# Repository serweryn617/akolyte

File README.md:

# Akolyte

⌨️ Low profile mechanical split keyboard

---

## Building firmware

Prerequisites:
 - `docker`

Firmware can be built using [cook-builder](https://github.com/serweryn617/cook):

**Setup:** initialize submodules and build Docker image. Has to be run only once:

```bash
cook setup
```

**Build:** build everything. Output files will be copied to the `output` directory:

```bash
cook
```

For complete list of commands run `cook -i`.

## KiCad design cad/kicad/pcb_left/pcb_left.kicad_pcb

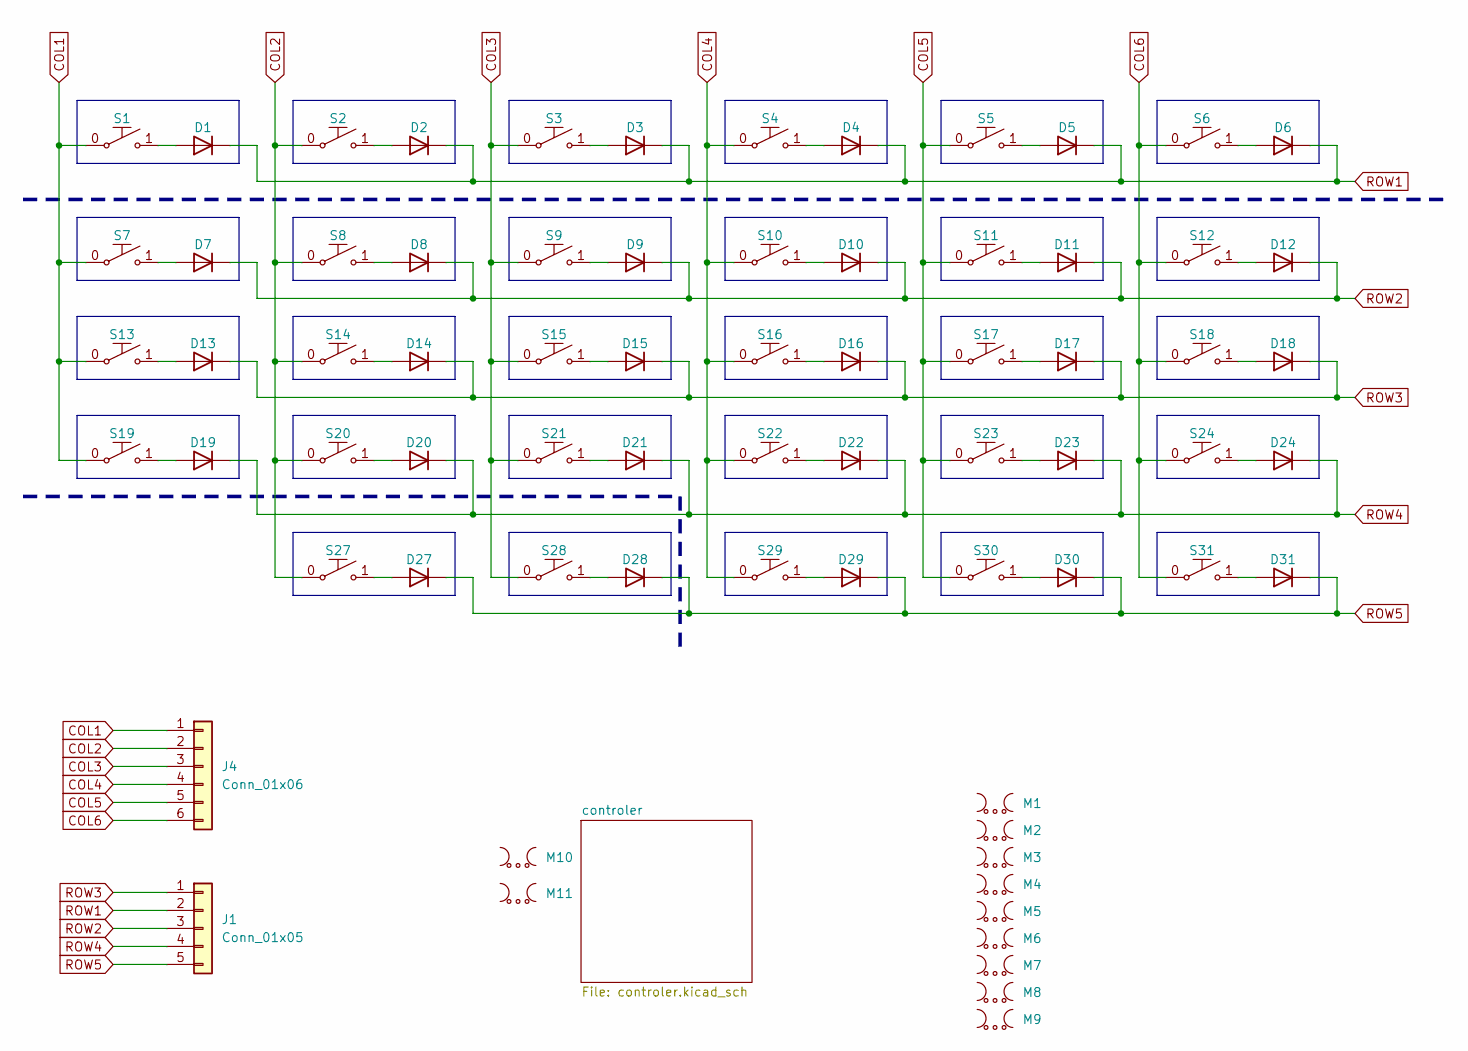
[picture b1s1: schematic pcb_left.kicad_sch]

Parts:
D1, D2, D3, D4, D5, D6, D7, D8, D9, D10, D11, D12, D13, D14, D15, D16, D17, D18, D19, D20, D21, D22, D23, D24, D27, D28, D29, D30, D31: 1N4148; SOD80_P5.5mm_Horizontal_SMD
J1: Conn_01x05; Row Connector
J4: Conn_01x06; Column Connector
M1, M2, M3, M4, M5, M6, M7, M8, M9, M10, M11: Mouse Bites
S1, S2, S3, S4, S5, S6, S7, S8, S9, S10, S11, S12, S13, S14, S15, S16, S17, S18, S19, S20, S21, S22, S23, S24, S27, S28, S29, S30, S31: Gateron_Switch; GATERON

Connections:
COL1: J4.1, S1.0, S7.0, S13.0, S19.0; also elsewhere on the board
COL2: J4.2, S2.0, S8.0, S14.0, S20.0, S27.0; also elsewhere on the board
COL3: J4.3, S3.0, S9.0, S15.0, S21.0, S28.0; also elsewhere on the board
COL4: J4.4, S4.0, S10.0, S16.0, S22.0, S29.0; also elsewhere on the board
COL5: J4.5, S5.0, S11.0, S17.0, S23.0, S30.0; also elsewhere on the board
COL6: J4.6, S6.0, S12.0, S18.0, S24.0, S31.0; also elsewhere on the board
unnamed: D1.2 (A), S1.1
unnamed: D2.2 (A), S2.1
unnamed: D3.2 (A), S3.1
unnamed: D4.2 (A), S4.1
unnamed: D5.2 (A), S5.1
unnamed: D6.2 (A), S6.1
unnamed: D7.2 (A), S7.1
unnamed: D8.2 (A), S8.1
unnamed: D9.2 (A), S9.1
unnamed: D10.2 (A), S10.1
unnamed: D11.2 (A), S11.1
unnamed: D12.2 (A), S12.1
unnamed: D13.2 (A), S13.1
unnamed: D14.2 (A), S14.1
unnamed: D15.2 (A), S15.1
unnamed: D16.2 (A), S16.1
unnamed: D17.2 (A), S17.1
unnamed: D18.2 (A), S18.1
unnamed: D19.2 (A), S19.1
unnamed: D20.2 (A), S20.1
unnamed: D21.2 (A), S21.1
unnamed: D22.2 (A), S22.1
unnamed: D23.2 (A), S23.1
unnamed: D24.2 (A), S24.1
unnamed: D27.2 (A), S27.1
unnamed: D28.2 (A), S28.1
unnamed: D29.2 (A), S29.1
unnamed: D30.2 (A), S30.1
unnamed: D31.2 (A), S31.1
ROW1: D1.1 (K), D2.1 (K), D3.1 (K), D4.1 (K), D5.1 (K), D6.1 (K), J1.2; also elsewhere on the board
ROW2: D7.1 (K), D8.1 (K), D9.1 (K), D10.1 (K), D11.1 (K), D12.1 (K), J1.3; also elsewhere on the board
ROW3: D13.1 (K), D14.1 (K), D15.1 (K), D16.1 (K), D17.1 (K), D18.1 (K), J1.1; also elsewhere on the board
ROW4: D19.1 (K), D20.1 (K), D21.1 (K), D22.1 (K), D23.1 (K), D24.1 (K), J1.4; also elsewhere on the board
ROW5: D27.1 (K), D28.1 (K), D29.1 (K), D30.1 (K), D31.1 (K), J1.5; also elsewhere on the board

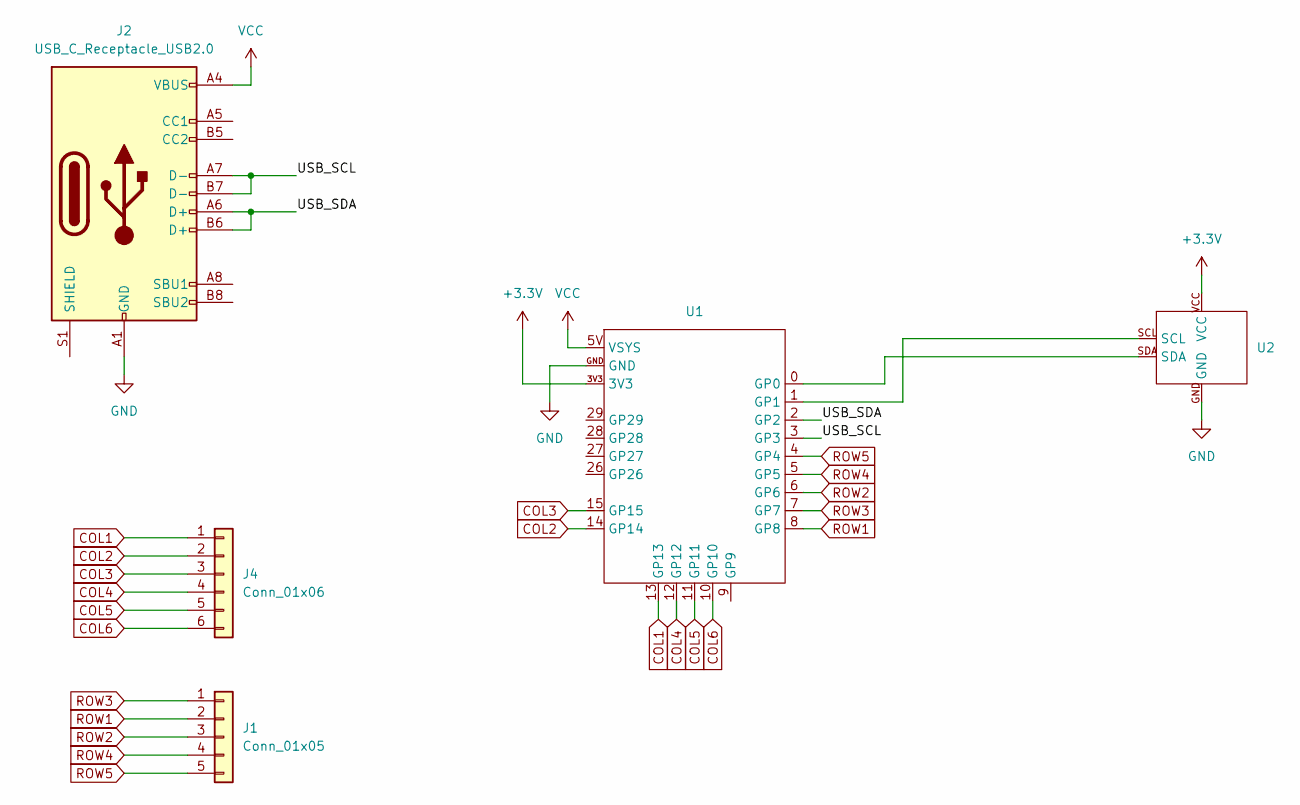
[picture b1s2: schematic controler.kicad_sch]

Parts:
J1: Conn_01x05; Row Connector
J2: USB_C_Receptacle_USB2.0; USB C Port
J4: Conn_01x06; Column Connector
U1: RP2040 - Zero
U2: OLED

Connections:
+3.3V: U1.3V3, U2.VCC
/controler/USB_SCL: J2.A7 (D-), J2.B7 (D-), U1.3 (GP3)
/controler/USB_SDA: J2.A6 (D+), J2.B6 (D+), U1.2 (GP2)
COL1: J4.1, U1.13 (GP13); also elsewhere on the board
COL2: J4.2, U1.14 (GP14); also elsewhere on the board
COL3: J4.3, U1.15 (GP15); also elsewhere on the board
COL4: J4.4, U1.12 (GP12); also elsewhere on the board
COL5: J4.5, U1.11 (GP11); also elsewhere on the board
COL6: J4.6, U1.10 (GP10); also elsewhere on the board
GND: J2.A1 (GND), J2.A12 (GND), J2.B1 (GND), J2.B12 (GND), U1.GND, U2.GND
unnamed: U1.0 (GP0), U2.SDA
unnamed: U1.1 (GP1), U2.SCL
ROW1: J1.2, U1.8 (GP8); also elsewhere on the board
ROW2: J1.3, U1.6 (GP6); also elsewhere on the board
ROW3: J1.1, U1.7 (GP7); also elsewhere on the board
ROW4: J1.4, U1.5 (GP5); also elsewhere on the board
ROW5: J1.5, U1.4 (GP4); also elsewhere on the board
VCC: J2.A4 (VBUS), J2.A9 (VBUS), J2.B4 (VBUS), J2.B9 (VBUS), U1.5V (VSYS)

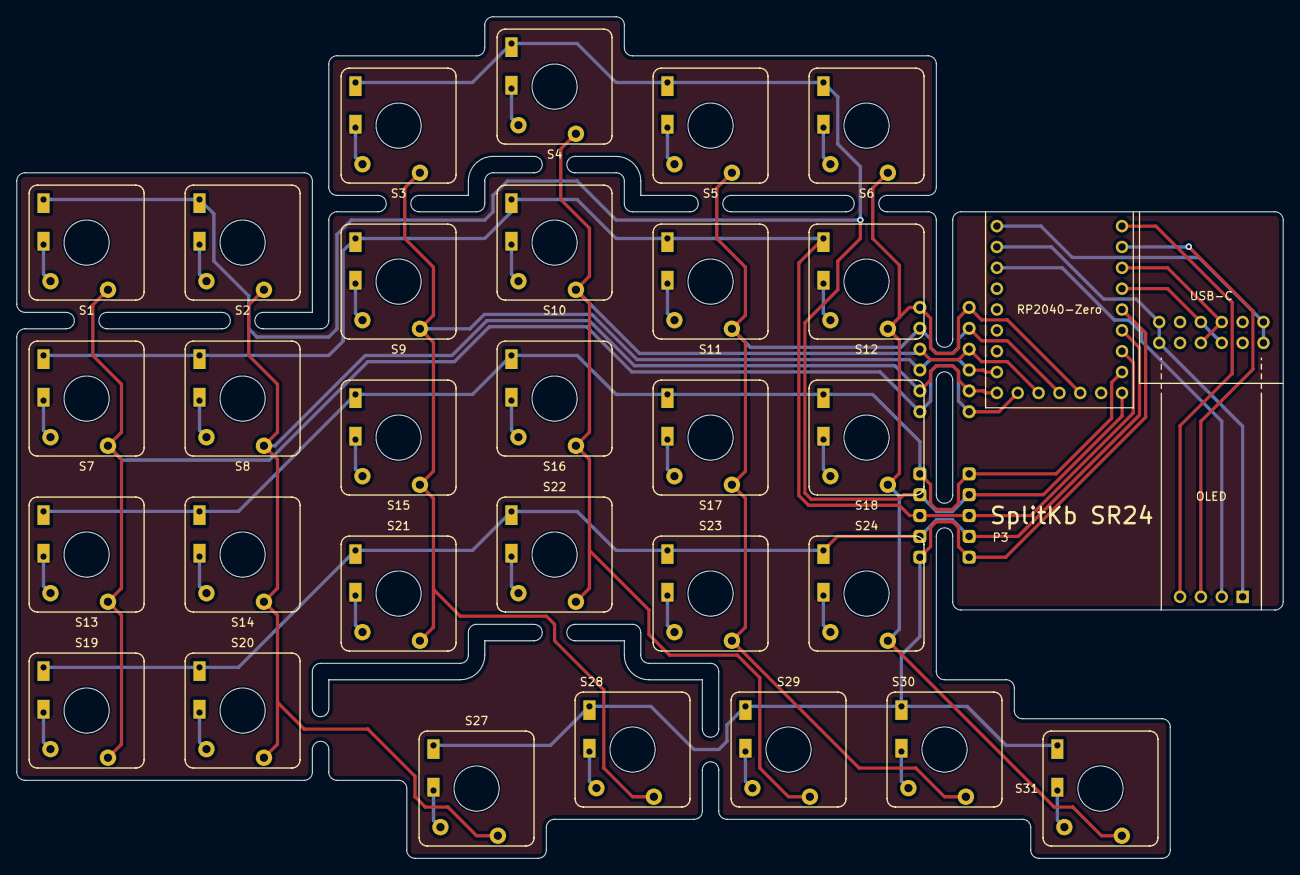
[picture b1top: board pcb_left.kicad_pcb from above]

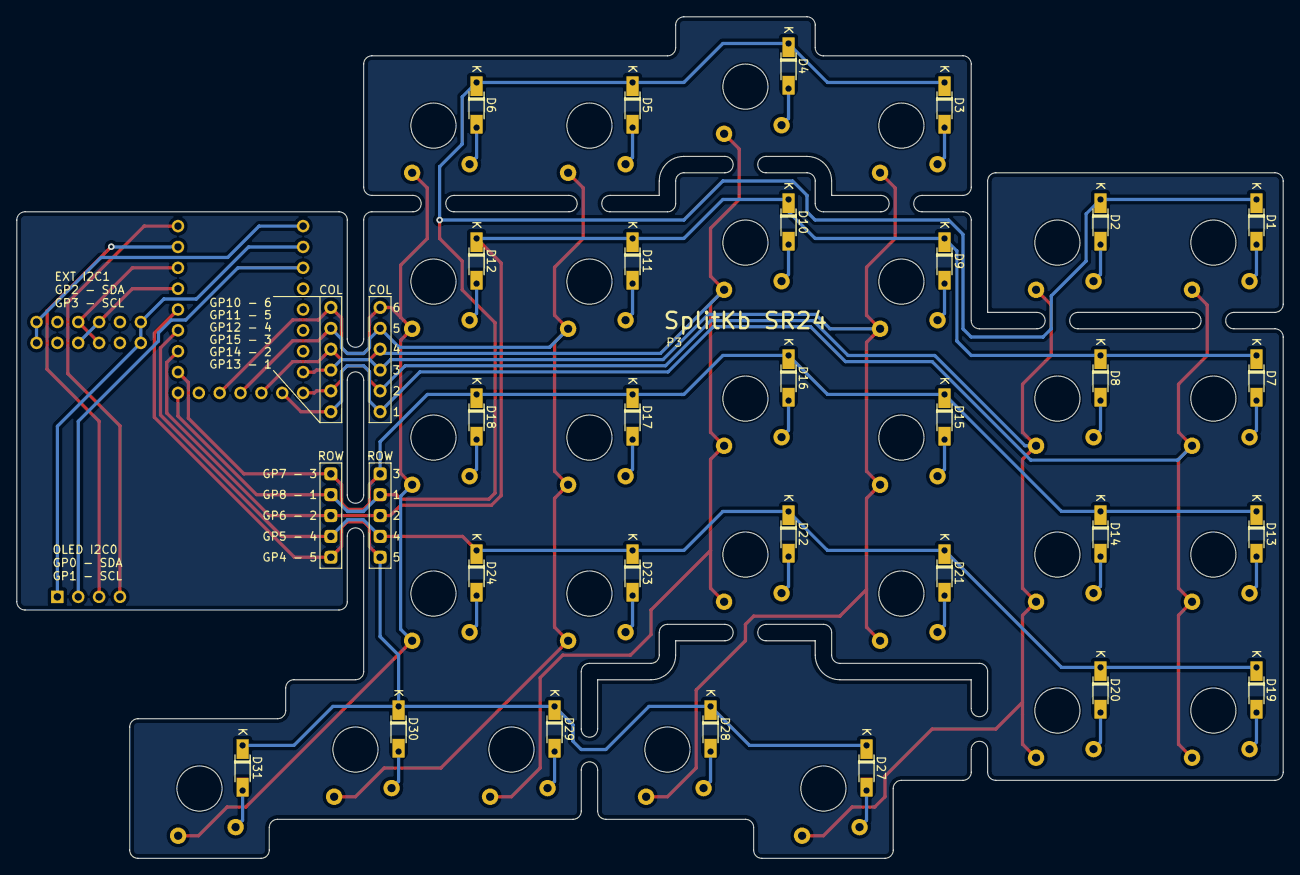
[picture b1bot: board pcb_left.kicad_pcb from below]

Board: 2 copper layers, 154.2 x 102.5 mm, 76 parts (33 on the bottom side), 47 nets.

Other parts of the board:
J5: Conn_01x06; Column Connector
J6: Conn_01x05; Row Connector

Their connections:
COL1: J5.1; also elsewhere on the board
COL2: J5.2; also elsewhere on the board
COL3: J5.3; also elsewhere on the board
COL4: J5.4; also elsewhere on the board
COL5: J5.5; also elsewhere on the board
COL6: J5.6; also elsewhere on the board
ROW1: J6.2; also elsewhere on the board
ROW2: J6.3; also elsewhere on the board
ROW3: J6.1; also elsewhere on the board
ROW4: J6.4; also elsewhere on the board
ROW5: J6.5; also elsewhere on the board

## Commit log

2024-07-16 Unify duplicate files
2024-07-16 Move build directory
2024-07-16 Cleanup recipe
2024-07-16 Add Pico SDK submodule
2024-07-16 Add submodule init
2024-07-16 Fix recipe; do a shallow clone
2024-07-16 Docker draft
2024-07-18 More updates
2024-07-18 Docker (#1)
    * Fix recipe; do a shallow clone
    * Docker draft
    * More updates
2024-09-15 Update recipe for new cook version
2024-09-15 Initial OLED driver
2024-09-15 Use I2C driver
2024-09-16 Update max data length
2024-09-16 oled working
2024-09-18 Oled support (#2)
    * Update recipe for new cook version
    * Initial OLED driver
    * Use I2C driver
    * Update max data length
    * oled working
2024-09-18 Font generation improvements
2024-09-18 ipc wip
2024-09-22 Basic IPC
2024-09-22 Ipc (#3)
    * ipc wip
    * Basic IPC
2024-09-22 Update font
2024-09-22 fix comments
2024-09-22 The Great Restructure
2024-09-22 Cleanup
2024-09-22 Update fonts
2024-09-24 Add command queue
2024-10-19 Adjust timings
2024-10-20 Defs lib
2024-10-20 Remove top row
2024-10-20 Basic layer info
2024-11-09 Increase delay
2024-11-09 Change layouts
2024-11-09 Templated fonts
2024-11-09 Add base layout switching
2025-03-22 Use side left right
2025-03-22 Rename
2025-03-22 Fix sides
2025-03-22 Add any usb side
2025-03-22 Remove preprocessor
2025-03-22 Add constexpr
2025-03-23 Add CRC
2025-03-23 Add communication layer
2025-03-23 Separate core 1 main
2025-03-23 I2C Commands WIP
2025-03-23 Update Pico SDK
2025-03-23 Add GIT
2025-03-23 Fix keycode copying
2025-03-23 I2C slave commands WIP
2025-03-24 Receive command buffer
2025-03-25 Worker work
2025-03-25 Use Ninja and C++20
2025-03-25 Update CRC lib
2025-03-25 Add variable payload length and crc to I2C commands
2025-03-26 Command validation
2025-04-02 Add UART
2025-04-02 Fix rare memcpy size overflow
2025-04-03 Led indicators
2025-04-05 CMaking
2025-04-05 Send OLED info over I2C
2025-04-12 Reduce I2C speed
2025-04-12 Remove leftovers
2025-04-12 Fix rare OLED core blocking
2025-04-12 Rename member
2025-04-12 I2c info (#5)
    * Send OLED info over I2C
    * Reduce I2C speed
    * Remove leftovers
    * Fix rare OLED core blocking
    * Rename member
2025-09-13 I2c info (#6)
    * Send OLED info over I2C
    * Reduce I2C speed
    * Remove leftovers
    * Fix rare OLED core blocking
    * Rename member
2025-09-13 wip (#8)
2025-09-13 Add chars_64
2025-09-13 True NKRO
